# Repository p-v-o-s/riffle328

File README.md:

riffle328
=========

"Riffle in a Bottle"

A lower-functionality / higher cost / Arduino IDE - compatible [Riffle](http://publiclab.org/wiki/riffle), based on Atmel328p.

- Requires FTDI cable for programming (e.g. Adafruit's "FTDI Friend") -- typically $15
- Includes uSD, flash memory, high-precision real time clock (DS3231) with coin battery backup
- Programmable as "Arduino UNO" in Arduino IDE
- runs at 3.3V and 16 MHz
- includes circuit for monitoring battery level
- board width allows device to be inserted through mouth of standard plastic water bottle (one with 20 mm diameter or greater)
- can run for several weeks (perhaps months) on 3 AA batteries, especially if low self-discharging batteries (like rechargeable Eneloops) are used
- Rough estimate of cost of parts that could be used to log temperature in a water bottle (not including shipping, or FTDI cable): $38 -- cost estimate [here](https://docs.google.com/spreadsheets/d/1v0O8HmP8-q_kPunHILv5Io3zThpqvPBZZoY3aYnxRDc/edit#gid=0)

### Usage

- For a diagram of pin locations and optional configurations, please see this [diagram in PDF format](https://github.com/p-v-o-s/riffle328/blob/master/riffleUsage.pdf)

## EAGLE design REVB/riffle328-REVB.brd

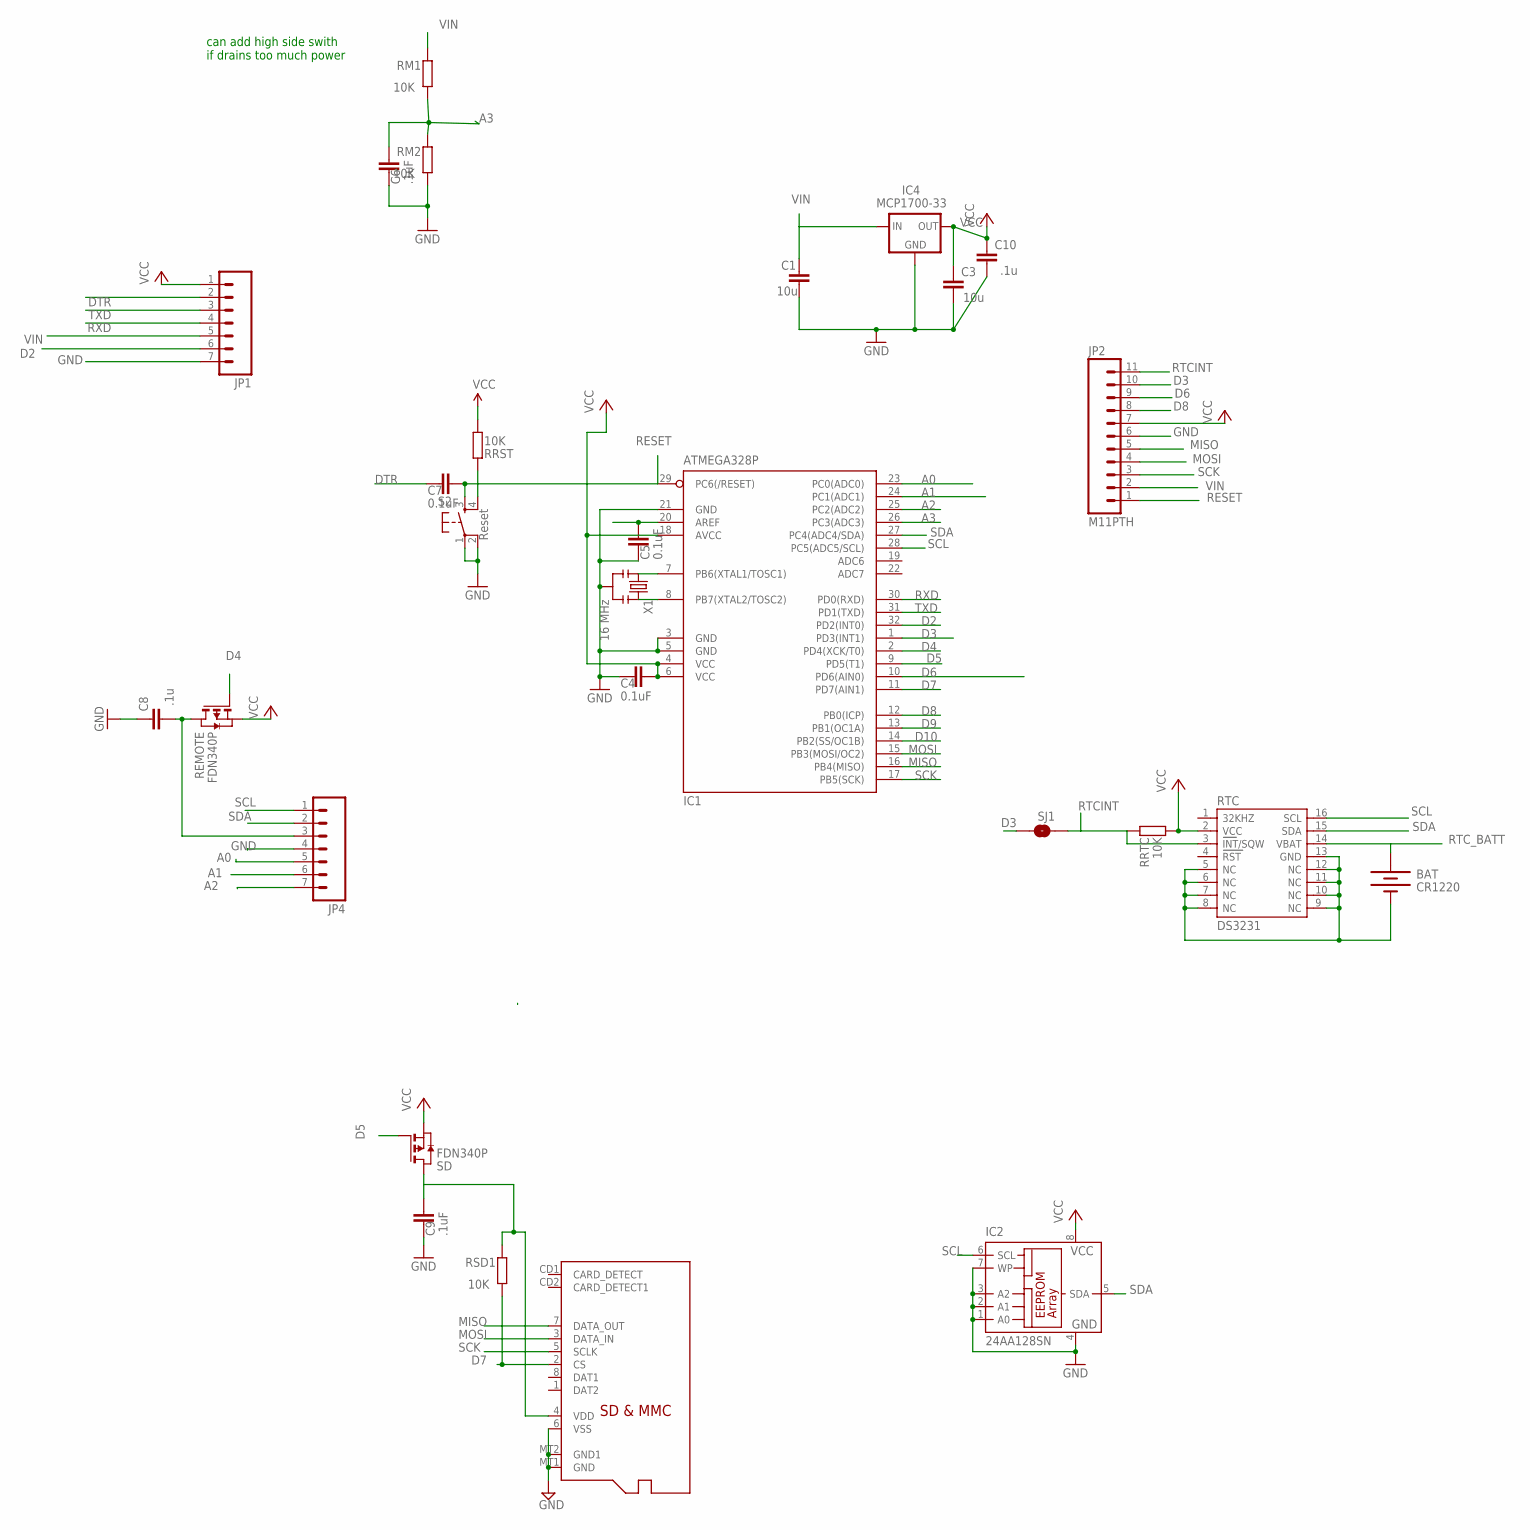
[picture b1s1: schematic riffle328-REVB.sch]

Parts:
BAT: CR1220; BATTCON_12MM_SMT
C1, C3: 10u; C0805
C4, C5, C7: 0.1uF; C0805@1
C6, C9: .1uF; C0805@1
C8, C10: .1u; C0805
IC1: ATMEGA328P; TQFP32-08
IC2: 24AA128SN; SO-08
IC4: MCP1700-33; SOT23
JP1, JP4: M07; 1X07
JP2: M11PTH; 1X11
MICROSD: MICROSD
REMOTE: FDN340P; SOT-23
RM1, RM2: 10K; R0805
RRST: 10K; R0805
RRTC: 10K; R0805
RSD1: 10K; R0805
RTC: DS3231
S2: Reset; TACTILE_SWITCH_SMD
SD: FDN340P; SOT-23
SJ1: SOLDERJUMPERNO; SJ_2S-NO
X1: 16 MHz; RESONATOR-SMD

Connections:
A0: IC1.23 (PC0(ADC0)), JP4.5
A1: IC1.24 (PC1(ADC1)), JP4.6
A2: IC1.25 (PC2(ADC2)), JP4.7
A3: C6.2, IC1.26 (PC3(ADC3)), RM1.1, RM2.2
AREF: C5.2, IC1.20 (AREF)
D2: IC1.32 (PD2(INT0)), JP1.6
D3: IC1.1 (PD3(INT1)), JP2.10, SJ1.2
D4: IC1.2 (PD4(XCK/T0)), REMOTE.3 (G)
D5: IC1.9 (PD5(T1)), SD.3 (G)
D6: IC1.10 (PD6(AIN0)), JP2.9
D7: IC1.11 (PD7(AIN1)), MICROSD.2 (CS), RSD1.1
D8: IC1.12 (PB0(ICP)), JP2.8
D9: IC1.13 (PB1(OC1A))
D10: IC1.14 (PB2(SS/OC1B))
DTR: C7.1, JP1.2
GND: BAT.P$1 (-), C1.2, C3.2, C4.1, C5.1, C6.1, C8.1, C9.1, C10.2, IC1.3 (GND), IC1.5 (GND), IC1.21 (GND), IC2.1 (A0), IC2.2 (A1), IC2.3 (A2), IC2.4 (GND), IC2.7 (WP), IC4.1 (GND), JP1.7, JP2.6, JP4.4, MICROSD.6 (VSS), MICROSD.MT1 (GND), MICROSD.MT2 (GND1), RM2.1, RTC.5 (NC), RTC.6 (NC), RTC.7 (NC), RTC.8 (NC), RTC.9 (NC), RTC.10 (NC), RTC.11 (NC), RTC.12 (NC), RTC.13 (GND), S2.1, S2.2, X1.2
MISO: IC1.16 (PB4(MISO)), JP2.5, MICROSD.7 (DATA_OUT)
MOSI: IC1.15 (PB3(MOSI/OC2)), JP2.4, MICROSD.3 (DATA_IN)
unnamed: IC1.8 (PB7(XTAL2/TOSC2)), X1.3
unnamed: IC1.7 (PB6(XTAL1/TOSC1)), X1.1
RESET: C7.2, IC1.29 (PC6(/RESET)), JP2.1, RRST.2, S2.3, S2.4
RTCINT: JP2.11, RRTC.2, RTC.3 (INT/SQW), SJ1.1
RTC_BATT: BAT.P$2 (+), RTC.14 (VBAT)
RXD: IC1.30 (PD0(RXD)), JP1.4
SCK: IC1.17 (PB5(SCK)), JP2.3, MICROSD.5 (SCLK)
SCL: IC1.28 (PC5(ADC5/SCL)), IC2.6 (SCL), JP4.1, RTC.16 (SCL)
SDA: IC1.27 (PC4(ADC4/SDA)), IC2.5 (SDA), JP4.2, RTC.15 (SDA)
TXD: IC1.31 (PD1(TXD)), JP1.3
VCC: C3.1, C4.2, C8.2, C10.1, IC1.4 (VCC), IC1.6 (VCC), IC1.18 (AVCC), IC2.8 (VCC), IC4.2 (OUT), JP1.1, JP2.7, JP4.3, REMOTE.1 (D), REMOTE.2 (S), RRST.1, RRTC.1, RTC.2 (VCC), SD.2 (S)
VDD: C9.2, MICROSD.4 (VDD), RSD1.2, SD.1 (D)
VIN: C1.1, IC4.3 (IN), JP1.5, JP2.2, RM1.2

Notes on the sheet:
can add high side swith if drains too much power

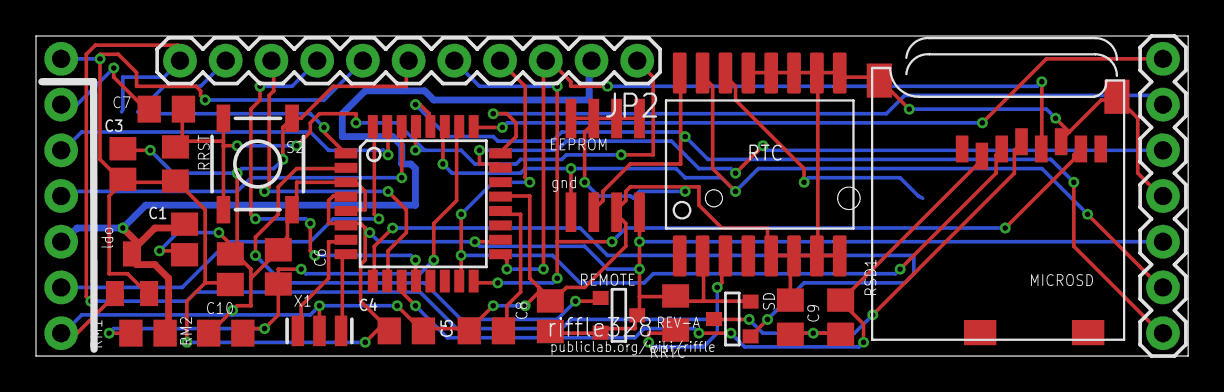
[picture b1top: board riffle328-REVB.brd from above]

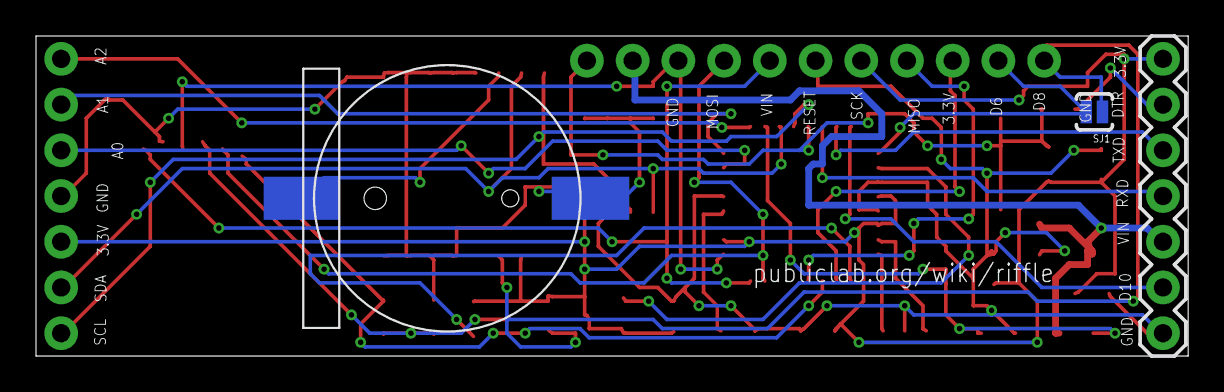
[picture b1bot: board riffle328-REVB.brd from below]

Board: 4 copper layers, 64.0 x 17.8 mm, 28 parts (3 on the bottom side), 29 nets.

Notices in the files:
parts and their libraries:
SparkFun-Connectors: Licensing: Creative Commons ShareAlike 4.0 International - https://creativecommons.org/licenses/by-sa/4.0
